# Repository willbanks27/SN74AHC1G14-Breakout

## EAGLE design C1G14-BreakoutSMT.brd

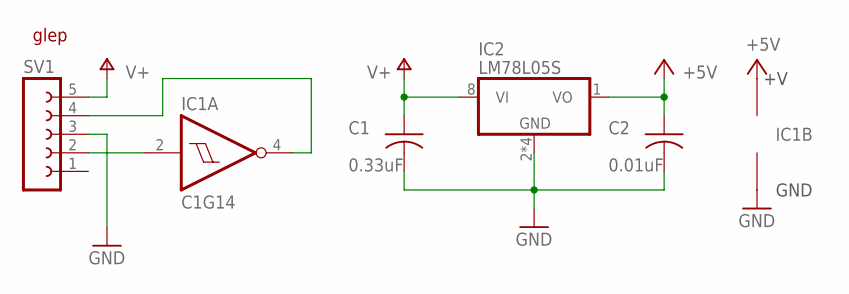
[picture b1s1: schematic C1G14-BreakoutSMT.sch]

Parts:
C1: 0.33uF; C0805
C2: 0.01uF; C0805
IC1: C1G14; SOT-25
IC2: LM78L05S; SO08
SV1: FE05-1
U$1: GLEP

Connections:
+5V: C2.1, IC1.5 (V+), IC2.1 (VO)
GND: C1.2, C2.2, IC1.3 (GND), IC2.2 (GND), IC2.3 (GND), IC2.6 (GND), IC2.7 (GND), SV1.3
unnamed: IC1.2 (A), SV1.2
unnamed: IC1.4 (Y), SV1.4
V+: C1.1, IC2.8 (VI), SV1.5

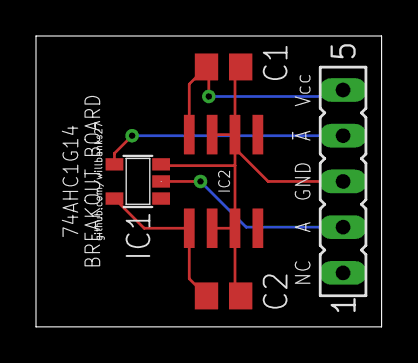
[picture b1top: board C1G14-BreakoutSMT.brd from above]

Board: 2 copper layers, 19.2 x 16.2 mm, 6 parts (1 on the bottom side), 5 nets.

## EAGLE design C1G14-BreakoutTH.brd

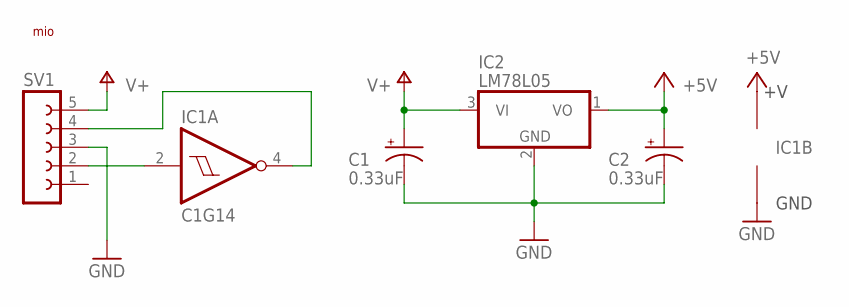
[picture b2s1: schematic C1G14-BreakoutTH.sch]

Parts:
C1, C2: 0.33uF; E2,5-6
IC1: C1G14; SOT-25
IC2: LM78L05; LM78LXX
SV1: FE05-1
U$2: MIO

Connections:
+5V: C2.+, IC1.5 (V+), IC2.1 (VO)
GND: C1.-, C2.-, IC1.3 (GND), IC2.2 (GND), SV1.3
unnamed: IC1.2 (A), SV1.2
unnamed: IC1.4 (Y), SV1.4
V+: C1.+, IC2.3 (VI), SV1.5

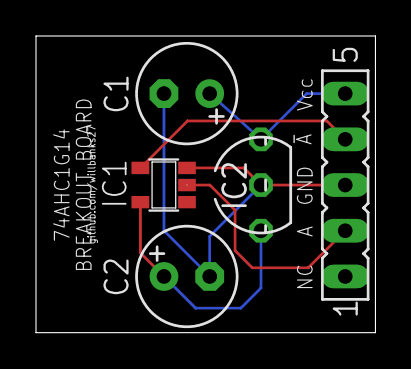
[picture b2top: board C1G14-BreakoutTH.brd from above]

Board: 2 copper layers, 18.9 x 16.5 mm, 6 parts (1 on the bottom side), 5 nets.
